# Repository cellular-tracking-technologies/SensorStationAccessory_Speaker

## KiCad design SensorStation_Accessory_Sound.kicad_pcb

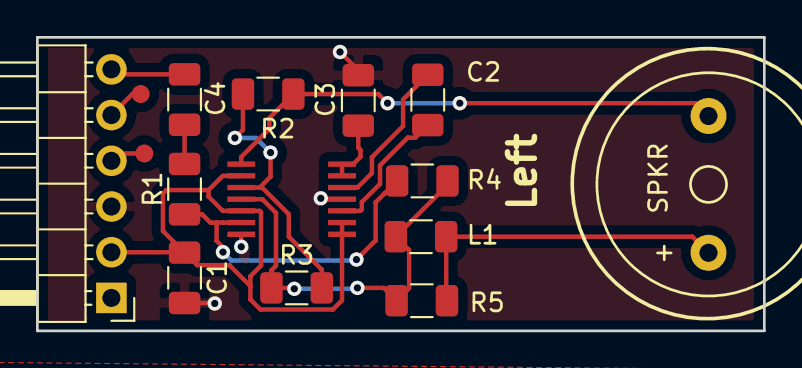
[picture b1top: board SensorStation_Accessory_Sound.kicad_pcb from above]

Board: 2 copper layers, 40.4 x 16.3 mm, 15 parts (0 on the bottom side), 14 nets.

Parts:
C1, C2, C3: 2.2u; C_1206_3216Metric
C4: 1u; C_1206_3216Metric
J1: SensorStation Accessory Plug; PinHeader_1x06_P2.54mm_Horizontal
L1: 100uH; L_1206_3216Metric
R1, R2, R3, R4: 10K; R_1206_3216Metric
R5: 10; R_1206_3216Metric
SPKR: Speaker; Buzzer_12x9.5RM7.6
TP1, TP2: TestPoint; Test_Point_Keystone_5019_Minature
U1: MAX4410; TSSOP14

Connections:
+3V3: C1.1, J1.2, U1.1, U1.2, U1.9, U1.12
CS: C4.1, J1.6
GND: C1.2, C3.2, J1.3, U1.4, U1.14
unnamed: C2.1, U1.3
unnamed: C2.2, U1.5
unnamed: C3.1, U1.6, U1.7
unnamed: C4.2, R1.1
unnamed: L1.1, R3.1, R4.1, R5.2, U1.11
unnamed: L1.2, R5.1, SPKR.1
unnamed: R2.1, SPKR.2, U1.8
unnamed: R1.2, R4.2, U1.13
unnamed: R2.2, R3.2, U1.10
SCL: J1.4, TP1.1
SDA: J1.5, TP2.1
